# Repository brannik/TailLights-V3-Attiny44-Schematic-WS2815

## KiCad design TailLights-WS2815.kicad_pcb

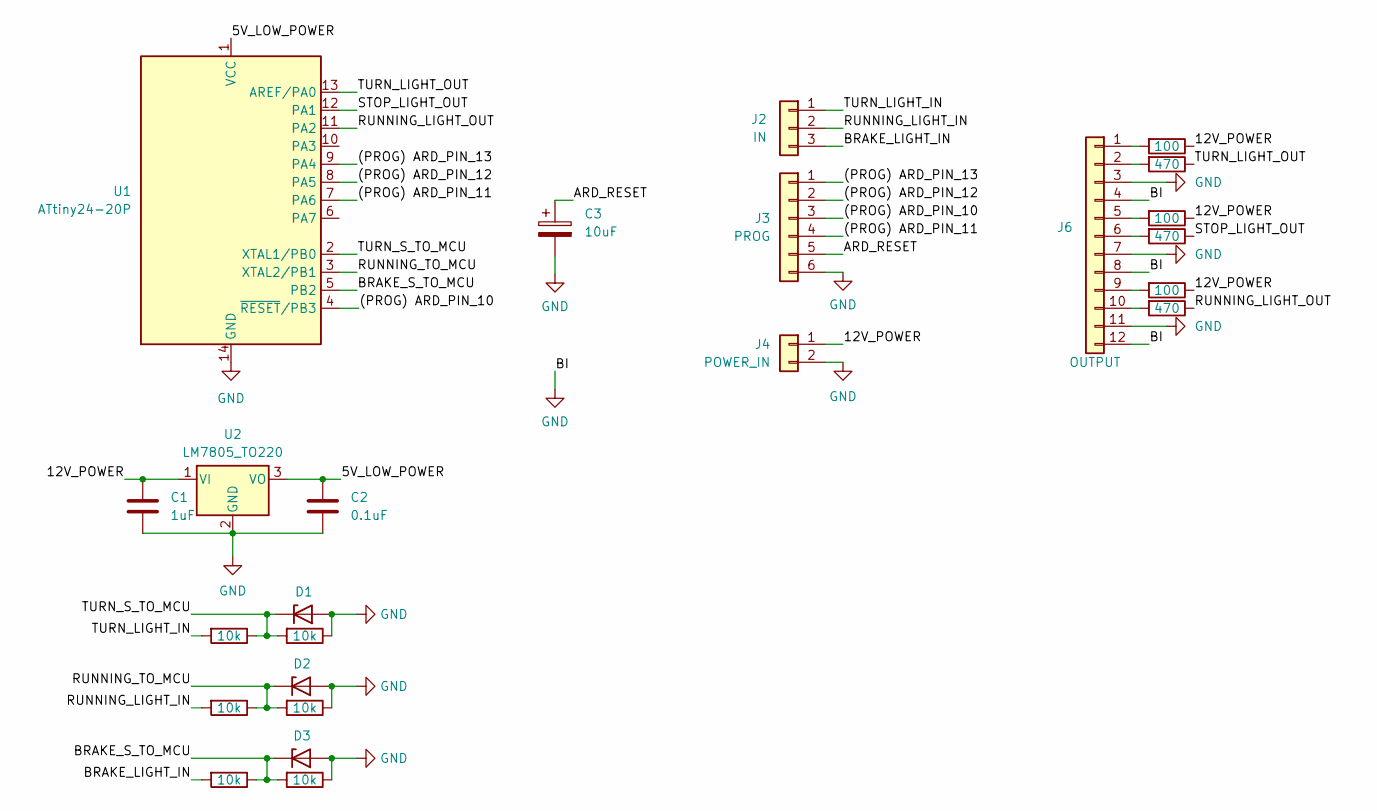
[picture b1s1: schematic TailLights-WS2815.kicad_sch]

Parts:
C1: 1uF; C_Disc_D10.0mm_W2.5mm_P5.00mm
C2: 0.1uF; C_Disc_D10.0mm_W2.5mm_P5.00mm
C3: 10uF; CP_Radial_D10.0mm_P5.00mm
D1, D2, D3: 1N47xxA; D_DO-41_SOD81_P3.81mm_Vertical_AnodeUp
J2: IN; PinSocket_1x03_P2.54mm_Vertical
J3: PROG; PinSocket_1x06_P2.54mm_Vertical
J4: POWER_IN; PinSocket_1x02_P2.54mm_Vertical
J6: OUTPUT; PinSocket_1x12_P2.54mm_Vertical
R1, R2, R3, R4, R5, R6: 10k; R_Axial_DIN0207_L6.3mm_D2.5mm_P2.54mm_Vertical
R7, R8, R9: 100; R_Axial_DIN0204_L3.6mm_D1.6mm_P7.62mm_Horizontal
R11, R12, R13: 470; R_Axial_DIN0204_L3.6mm_D1.6mm_P7.62mm_Horizontal
U1: ATtiny24-20P; DIP-14_W7.62mm
U2: LM7805_TO220; TO-220-3_Vertical

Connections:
/5V_LOW_POWER: C2.1, U1.1 (VCC), U2.3 (VO)
/12V_POWER: C1.1, J4.1, R7.1, R8.1, R9.1, U2.1 (VI)
/(PROG) ARD_PIN_10: J3.3, U1.4 (~RESET/PB3)
/(PROG) ARD_PIN_11: J3.4, U1.7 (PA6)
/(PROG) ARD_PIN_12: J3.2, U1.8 (PA5)
/(PROG) ARD_PIN_13: J3.1, U1.9 (PA4)
/ARD_RESET: C3.1, J3.5
/BRAKE_LIGHT_IN: J2.3, R5.2
/BRAKE_S_TO_MCU: D3.1 (K), R5.1, R6.2, U1.5 (PB2)
/RUNNING_LIGHT_IN: J2.2, R3.2
/RUNNING_LIGHT_OUT: R13.1, U1.11 (PA2)
/RUNNING_TO_MCU: D2.1 (K), R3.1, R4.2, U1.3 (XTAL2/PB1)
/STOP_LIGHT_OUT: R12.1, U1.12 (PA1)
/TURN_LIGHT_IN: J2.1, R1.2
/TURN_LIGHT_OUT: R11.1, U1.13 (AREF/PA0)
/TURN_S_TO_MCU: D1.1 (K), R1.1, R2.2, U1.2 (XTAL1/PB0)
GND: C1.2, C2.2, C3.2, D1.2 (A), D2.2 (A), D3.2 (A), J3.6, J4.2, J6.3, J6.4, J6.7, J6.8, J6.11, J6.12, R2.1, R4.1, R6.1, U1.14 (GND), U2.2 (GND)
unnamed: J6.1, R7.2
unnamed: J6.2, R11.2
unnamed: J6.5, R8.2
unnamed: J6.6, R12.2
unnamed: J6.9, R9.2
unnamed: J6.10, R13.2

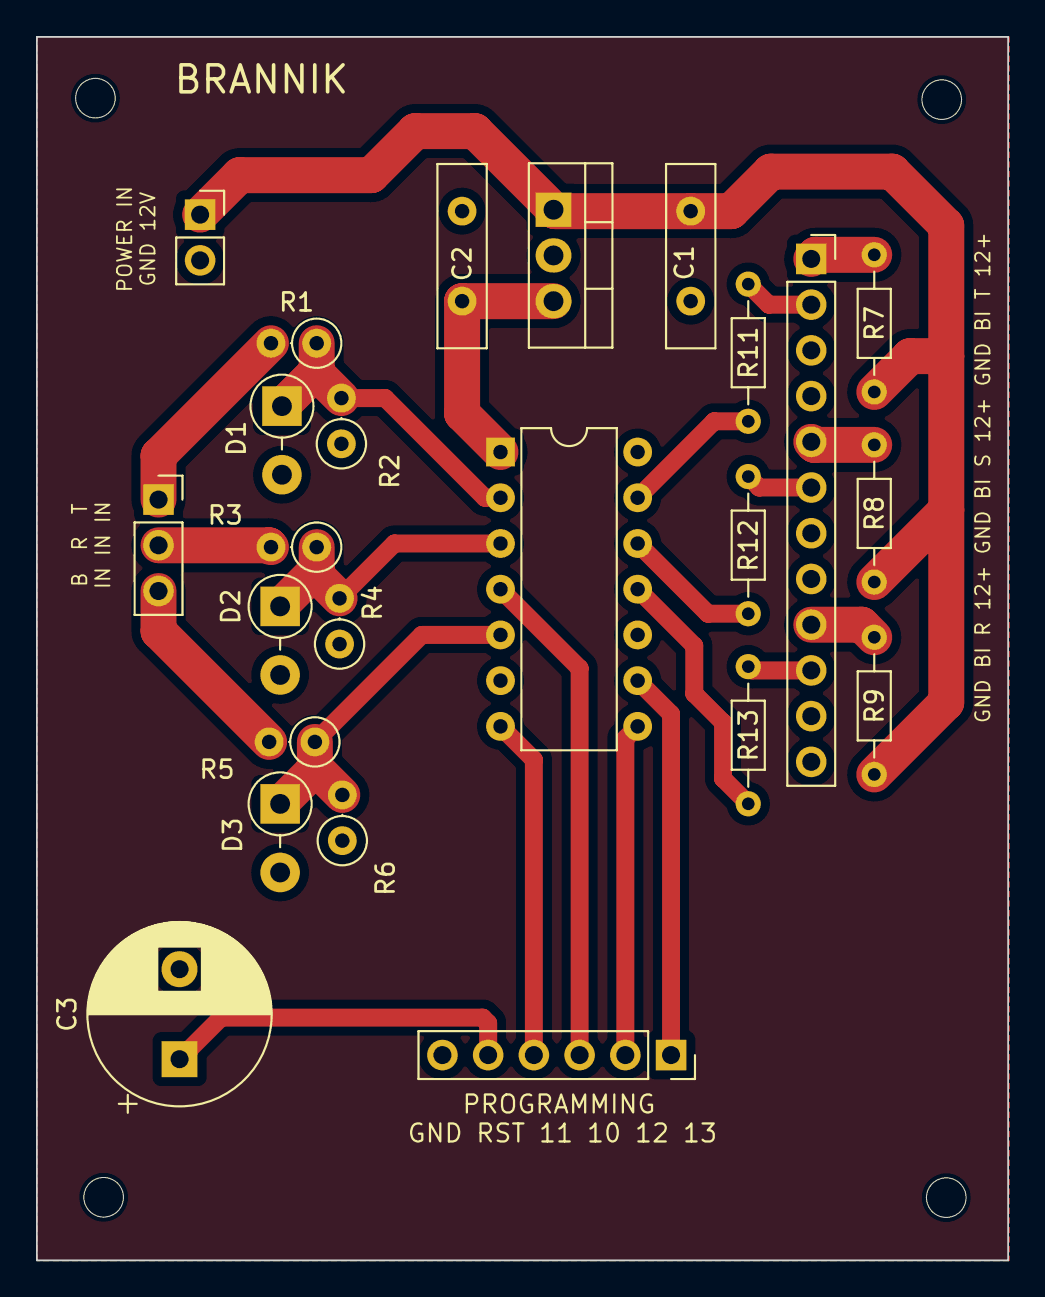
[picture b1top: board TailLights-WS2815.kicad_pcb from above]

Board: 2 copper layers, 54.0 x 68.0 mm, 24 parts (0 on the bottom side), 23 nets.

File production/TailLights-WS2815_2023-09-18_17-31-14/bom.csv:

Designator,Footprint,Quantity,Value,LCSC Part #
C1,C_Disc_D10.0mm_W2.5mm_P5.00mm,1,1uF,
C2,C_Disc_D10.0mm_W2.5mm_P5.00mm,1,0.1uF,
C3,CP_Radial_D10.0mm_P5.00mm,1,10uF,
"D1, D2, D3",D_DO-41_SOD81_P3.81mm_Vertical_AnodeUp,3,1N47xxA,
J2,PinSocket_1x03_P2.54mm_Vertical,1,IN,
J3,PinSocket_1x06_P2.54mm_Vertical,1,PROG,
J4,PinSocket_1x02_P2.54mm_Vertical,1,POWER_IN,
J6,PinSocket_1x12_P2.54mm_Vertical,1,OUTPUT,
"R1, R2, R3, R4, R5, R6",R_Axial_DIN0207_L6.3mm_D2.5mm_P2.54mm_Vertical,6,10k,
"R11, R12, R13",R_Axial_DIN0204_L3.6mm_D1.6mm_P7.62mm_Horizontal,3,470,
"R7, R8, R9",R_Axial_DIN0204_L3.6mm_D1.6mm_P7.62mm_Horizontal,3,100,
U1,DIP-14_W7.62mm,1,ATtiny24-20P,
U2,TO-220-3_Vertical,1,LM7805_TO220,

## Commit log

2023-09-18 init
